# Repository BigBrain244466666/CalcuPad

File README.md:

# CalcuPad

CalcuPad is a 10 key macropad that includes all the digits 0-9.

It's very basic as it is my first build, but I guess you could say it has all the digits you ever need.

# CAD

This macropad has two 3D printed layers, a top and a bottom, it is a very simple design, with some LED lights and 10 keys.

# PCB and Schematic

Used KiCAD

# Firmware

Used KMK for the firmware. The numbers input any number that is pressed, and the lights light up everytime you press a button.

# BOM

- 10x Cherry MX Switches
- 10x DSA Keycaps
- 6x SK6812 MINI-E LEDs
- 4x M3x16mm screws
- 4x M3x5mx4mm heatset inserts
- 1x Seeed XIAO RP2040

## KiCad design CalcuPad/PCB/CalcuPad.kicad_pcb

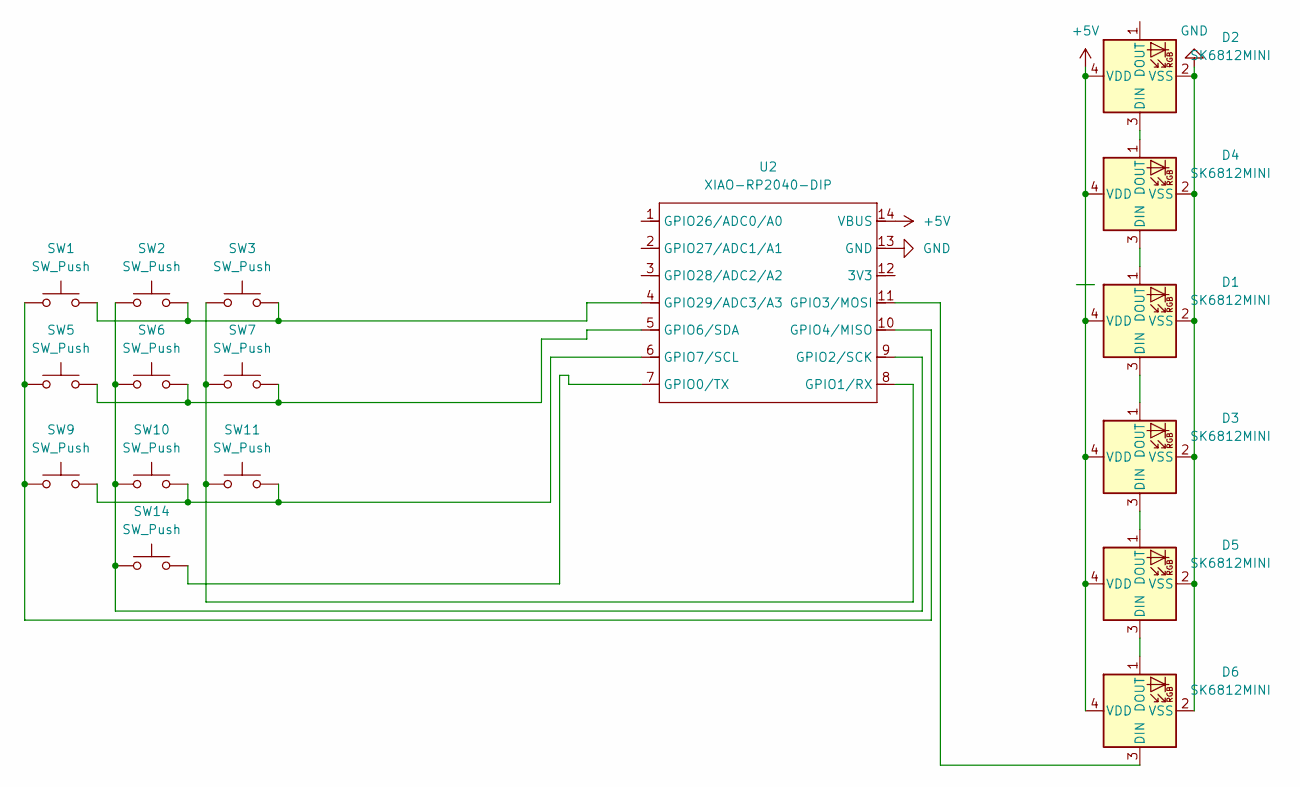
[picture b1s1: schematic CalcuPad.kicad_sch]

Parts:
D1, D2, D3, D4, D5, D6: SK6812MINI; LED_SK6812MINI_PLCC4_3.5x3.5mm_P1.75mm
SW1, SW2, SW3, SW5, SW6, SW7, SW9, SW10, SW11, SW14: SW_Push; SW_Cherry_MX_1.00u_PCB
U2: XIAO-RP2040-DIP

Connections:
+5V: D1.4 (VDD), D2.4 (VDD), D3.4 (VDD), D4.4 (VDD), D5.4 (VDD), D6.4 (VDD), U2.14 (VBUS)
GND: D1.2 (VSS), D2.2 (VSS), D3.2 (VSS), D4.2 (VSS), D5.2 (VSS), D6.2 (VSS), U2.13 (GND)
unnamed: D1.3 (DIN), D3.1 (DOUT)
unnamed: D1.1 (DOUT), D4.3 (DIN)
unnamed: D2.3 (DIN), D4.1 (DOUT)
unnamed: D3.3 (DIN), D5.1 (DOUT)
unnamed: D5.3 (DIN), D6.1 (DOUT)
unnamed: D6.3 (DIN), U2.11 (GPIO3/MOSI)
unnamed: SW14.2, U2.7 (GPIO0/TX)
unnamed: SW3.1, SW7.1, SW11.1, U2.8 (GPIO1/RX)
unnamed: SW2.1, SW6.1, SW10.1, SW14.1, U2.9 (GPIO2/SCK)
unnamed: SW1.1, SW5.1, SW9.1, U2.10 (GPIO4/MISO)
unnamed: SW5.2, SW6.2, SW7.2, U2.5 (GPIO6/SDA)
unnamed: SW9.2, SW10.2, SW11.2, U2.6 (GPIO7/SCL)
unnamed: SW1.2, SW2.2, SW3.2, U2.4 (GPIO29/ADC3/A3)

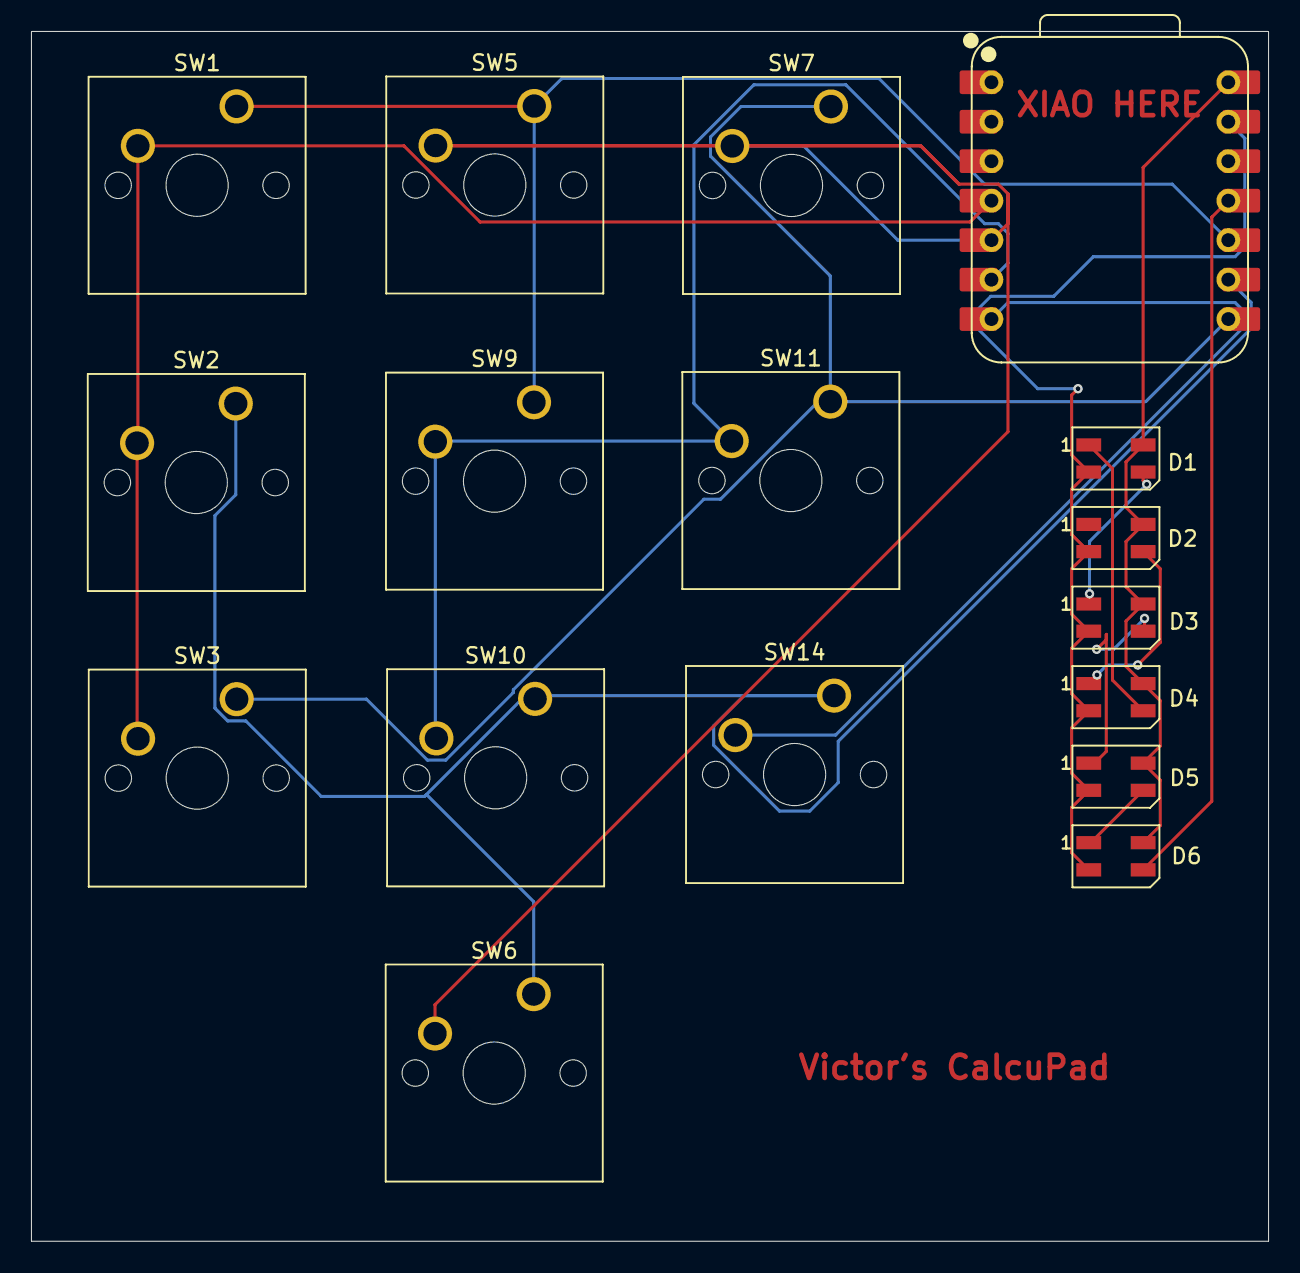
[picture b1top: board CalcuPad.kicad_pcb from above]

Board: 2 copper layers, 79.6 x 77.9 mm, 17 parts (0 on the bottom side), 15 nets.
